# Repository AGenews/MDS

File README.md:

# Motion Detector Shield
A simplified microwave-based motion detector for home cage activity monitoring in mice.

<a href="https://oshpark.com/shared_projects/rqF87nvL"></img></a>

MIT License

Copyright (c) [2017] [Andreas Genewsky]

Permission is hereby granted, free of charge, to any person obtaining a copy
of this software and associated documentation files (the "Software"), to deal
in the Software without restriction, including without limitation the rights
to use, copy, modify, merge, publish, distribute, sublicense, and/or sell
copies of the Software, and to permit persons to whom the Software is
furnished to do so, subject to the following conditions:

The above copyright notice and this permission notice shall be included in all
copies or substantial portions of the Software.

THE SOFTWARE IS PROVIDED "AS IS", WITHOUT WARRANTY OF ANY KIND, EXPRESS OR
IMPLIED, INCLUDING BUT NOT LIMITED TO THE WARRANTIES OF MERCHANTABILITY,
FITNESS FOR A PARTICULAR PURPOSE AND NONINFRINGEMENT. IN NO EVENT SHALL THE
AUTHORS OR COPYRIGHT HOLDERS BE LIABLE FOR ANY CLAIM, DAMAGES OR OTHER
LIABILITY, WHETHER IN AN ACTION OF CONTRACT, TORT OR OTHERWISE, ARISING FROM,
OUT OF OR IN CONNECTION WITH THE SOFTWARE OR THE USE OR OTHER DEALINGS IN THE
SOFTWARE.

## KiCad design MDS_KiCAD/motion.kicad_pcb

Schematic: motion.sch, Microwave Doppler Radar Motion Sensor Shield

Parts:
AD1: AD1; Socket_Strip_Straight_1x03
AD2: AD2; Socket_Strip_Straight_1x03
AD3: AD3; Socket_Strip_Straight_1x03
C1, C2, C3, C4, C5, C6: 22µF; C_Radial_D5_L11_P2
D1: 1N4148; Diode_DO-35_SOD27_Horizontal_RM10
D2, D3, D4, D5, D6: D; Diode_DO-35_SOD27_Horizontal_RM10
D7, D8, D9, D10, D11, D12: LED; LED-3MM
IC1, IC2, IC3: SN74LS423; DIP-16_W7.62mm_LongPads
P1: SENSOR_A; Socket_Strip_Straight_1x04
P2: SENSOR_B; Socket_Strip_Straight_1x04
P3: SENSOR_C; Socket_Strip_Straight_1x04
P4: SENSOR_D; Socket_Strip_Straight_1x04
P5: SENSOR_E; Socket_Strip_Straight_1x04
P6: SENSOR_F; Socket_Strip_Straight_1x04
Q1: TEMT6000; R_1206_HandSoldering
R1, R14, R15, R16, R17, R18, R19, R20: 10K; R_0805_HandSoldering
R2, R3, R8, R9, R10, R13: 2.2K; R_0805_HandSoldering
R4, R5, R6, R7, R11, R12: 220K; R_0805_HandSoldering
SHIELD1: MDR_SHIELD; ARDUINO_SHIELD_2

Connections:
(MISO): SHIELD1.12
(MOSI): SHIELD1.11
(RTC_SCL): SHIELD1.AD5
(RTC_SDA): SHIELD1.AD4
(SCK): SHIELD1.13
(SD_CS): SHIELD1.10
+5V: AD1.1, AD2.1, AD3.1, IC1.16, IC2.16, IC3.16, P1.1, P1.3, P2.1, P2.3, P3.1, P3.3, P4.1, P4.3, P5.1, P5.3, P6.1, P6.3, Q1.2 (C), R2.2, R3.2, R4.2, R5.2, R6.2, R7.2, R8.2, R9.2, R10.2, R11.2, R12.2, R13.2, SHIELD1.5V
AD1: AD1.3, SHIELD1.AD1
AD2: AD2.3, SHIELD1.AD2
AD3: AD3.3, SHIELD1.AD3
AMBIENT_LIGHT: Q1.1 (E), R14.1, SHIELD1.AD0
GNDREF: AD1.2, AD2.2, AD3.2, IC1.1, IC1.8, IC1.9, IC2.1, IC2.8, IC2.9, IC3.1, IC3.8, IC3.9, P1.4, P2.4, P3.4, P4.4, P5.4, P6.4, R1.2, R14.2, R15.2, R16.2, R17.2, R18.2, R19.2, R20.2, SHIELD1.GND1, SHIELD1.GND2, SHIELD1.GND3
unnamed: C1.1, IC1.15, R4.1
unnamed: C1.2, IC1.14
unnamed: C2.1, IC2.15, R5.1
unnamed: C2.2, IC2.14
unnamed: C3.1, IC1.7, R6.1
unnamed: C3.2, IC1.6
unnamed: C4.1, IC2.7, R7.1
unnamed: C4.2, IC2.6
unnamed: C5.1, IC3.15, R11.1
unnamed: C5.2, IC3.14
unnamed: C6.1, IC3.7, R12.1
unnamed: C6.2, IC3.6
unnamed: D1.1, D2.1, D3.1, D4.1, D5.1, D6.1, R1.1, SHIELD1.2
unnamed: D7.1, IC1.4
unnamed: D7.2, R2.1
unnamed: D8.1, IC2.4
unnamed: D8.2, R3.1
unnamed: D9.1, IC1.12
unnamed: D9.2, R8.1
unnamed: D10.1, IC2.12
unnamed: D10.2, R9.1
unnamed: D11.1, IC3.4
unnamed: D11.2, R10.1
unnamed: D12.1, IC3.12
unnamed: D12.2, R13.1
SENS_A: D1.2, IC1.2, P1.2, R17.1
SENS_B: D2.2, IC2.2, P2.2, R15.1
SENS_C: D3.2, IC3.2, P3.2, R16.1
SENS_D: D4.2, IC1.10, P4.2, R18.1
SENS_E: D5.2, IC2.10, P5.2, R19.1
SENS_F: D6.2, IC3.10, P6.2, R20.1
flopA: IC1.13, SHIELD1.3
flopB: IC2.13, SHIELD1.4
flopC: IC3.13, SHIELD1.5
flopD: IC1.5, SHIELD1.6
flopE: IC2.5, SHIELD1.7
flopF: IC3.5, SHIELD1.8
flopRST: IC1.3, IC1.11, IC2.3, IC2.11, IC3.3, IC3.11, SHIELD1.9

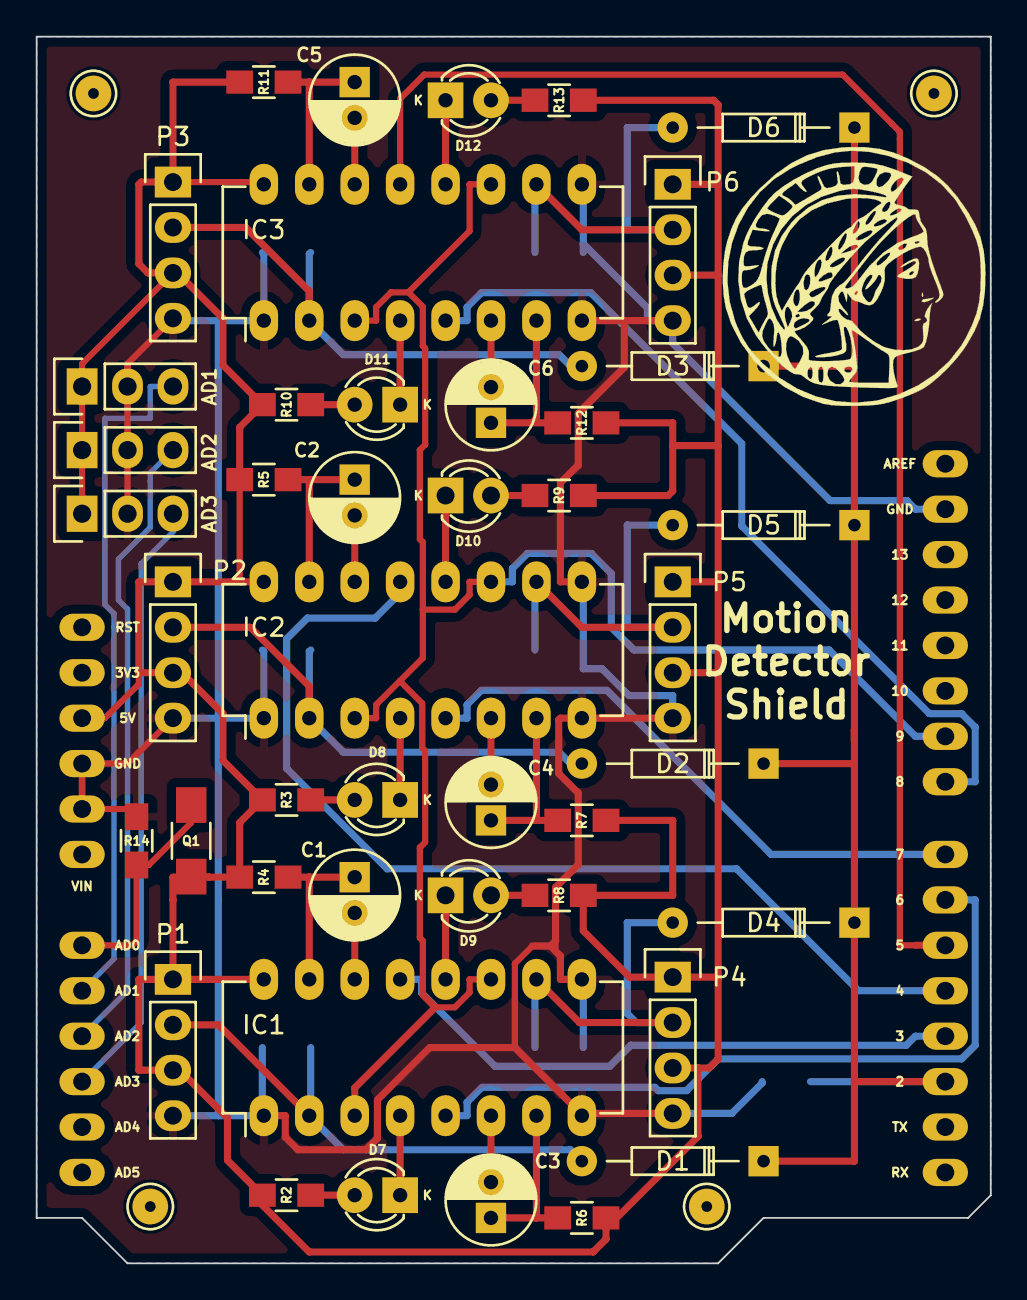
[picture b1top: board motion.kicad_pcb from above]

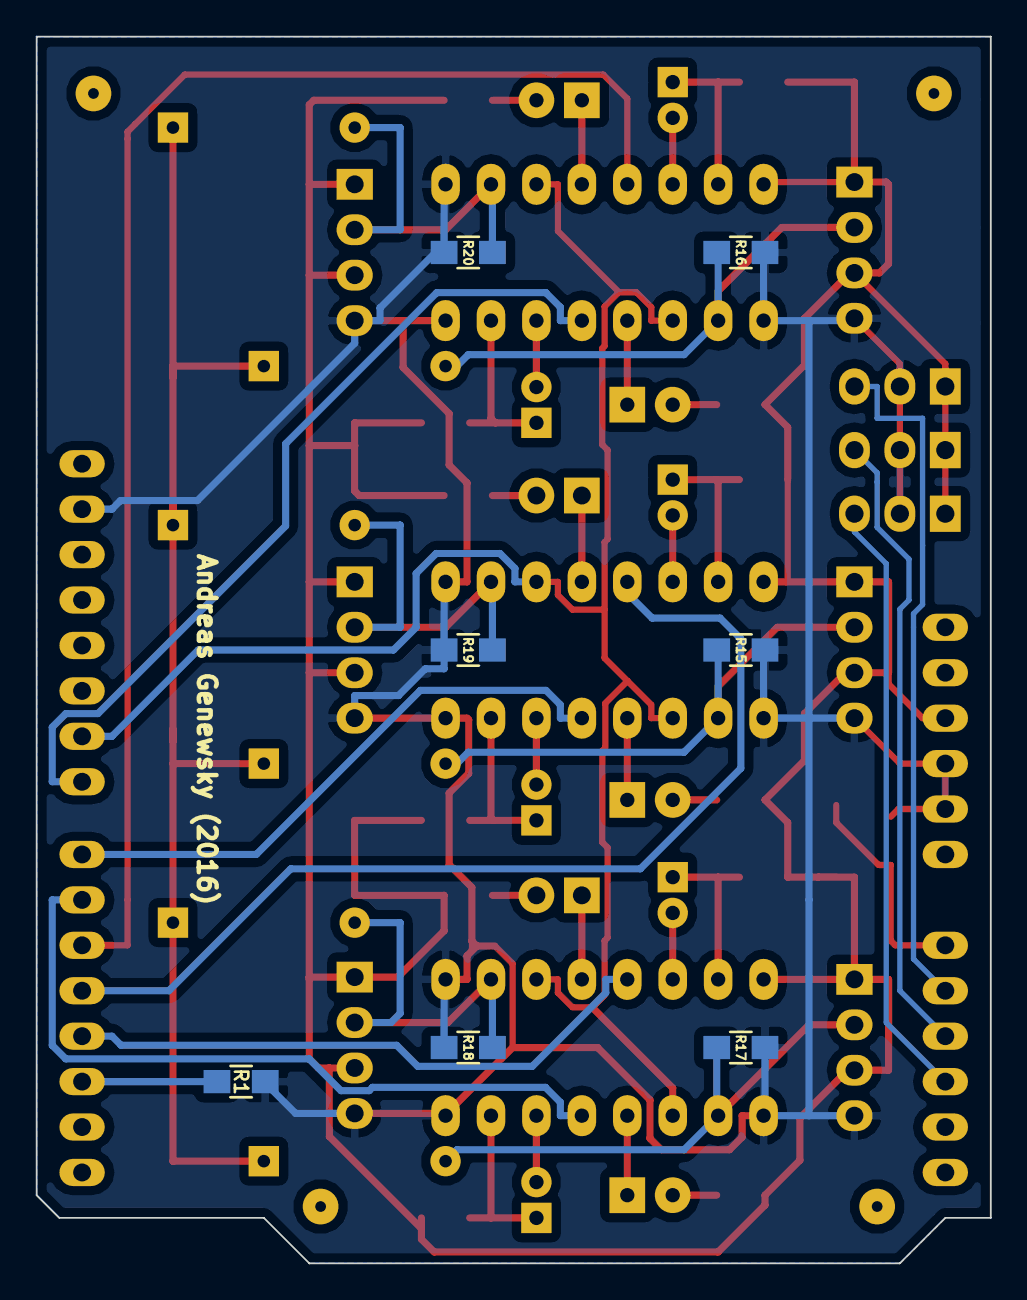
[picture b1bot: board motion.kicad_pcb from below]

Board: 2 copper layers, 53.3 x 68.6 mm, 52 parts (7 on the bottom side), 44 nets.

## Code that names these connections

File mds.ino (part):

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#define ECHO_TO_SERIAL   1 // echo data to serial port
#define WRITE_TO_SD   1 // initialize SD and write data to SD

int flopRST = 9;  // SN74LS423 RESET Pin ... read SN74LS423 documentation
int SENS_A = 3;   // channel A 
int SENS_B = 4;   // channel B
int SENS_C = 5;   // channel C
int SENS_D = 6;   // channel D
int SENS_E = 7;   // channel E
int SENS_F = 8;   // channel F
int AMBIENT = 14; // corresponds to A0 on Arduino UNO, TEMT6000 lightsensor
int AD1 = 15;     // optional analog input
int AD2 = 16;     // optional analog input
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  bootup = millis(); 
  
  // no we set the INPUT & OUTPUT Pins
  pinMode(flopRST, OUTPUT);
  pinMode(SENS_A, INPUT);
  pinMode(SENS_B, INPUT);
  pinMode(SENS_C, INPUT);
  pinMode(SENS_D, INPUT);
  pinMode(SENS_E, INPUT);
  pinMode(SENS_F, INPUT);
  pinMode(AMBIENT, INPUT);
  pinMode(AD1, INPUT);
  pinMode(AD2, INPUT);
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
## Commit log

2016-08-30 Added Gerber files Rev0.2
2016-08-30 Added Arduino Code
2016-08-30 Added Python Code
2017-06-02 Updated license.
2017-06-05 Uploaded KiCAD design files.
2017-06-05 Uploaded RAW data.
2017-06-05 Uploaded compressed RAW data.
2017-06-05 Uploaded compressed RAW data as *.zip* file.
2017-06-05 Update motion_analysis.py
    I've put the print (...) in line 88 in brackets, as this seems to avoid throwing an error before the usage commands appear.
2017-08-18 Corrected a Bug
2017-08-18 Update motion_analysis.py
    Now allows to use millisecond bins.
